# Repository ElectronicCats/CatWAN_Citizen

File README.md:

# CatWAN Citizen Sensor Board

LoRa Smart city sensor, based on open hardware and free software, generating and sharing real open data on air pollution, acoustics and many more, compatible with LoRa and LoRaWAN.

## Sensor list

|Metric|Units|Sensor|
|-|:-:|:-:|
| **Atmospheric Pressure** | Pa | BME280 |
| **Air Temperature / Relative Humidity** | ºC / %rh | BME280|
| **CO, eCO2** | ppm |AMS CCS811|
| **Noise Level and Spectrum** | dBa |Microphone|
| **Ambient Light** | lx | Rohm BEML6075 |

## LICENSE
Firmware released under an GNU AGPL v3.0 license. See the LICENSE file for more information.

Hardware released under an CERN Open Hardware Licence v1.2. See the LICENSE_HARDWARE file for more information.

Designed by Electronic Cats.

Electronic Cats is a registered trademark, please do not use if you sell these PCBs.

Electronic Cats invests time and resources providing this open source design, please support Electronic Cats and open-source hardware by purchasing products from Electronic Cats!

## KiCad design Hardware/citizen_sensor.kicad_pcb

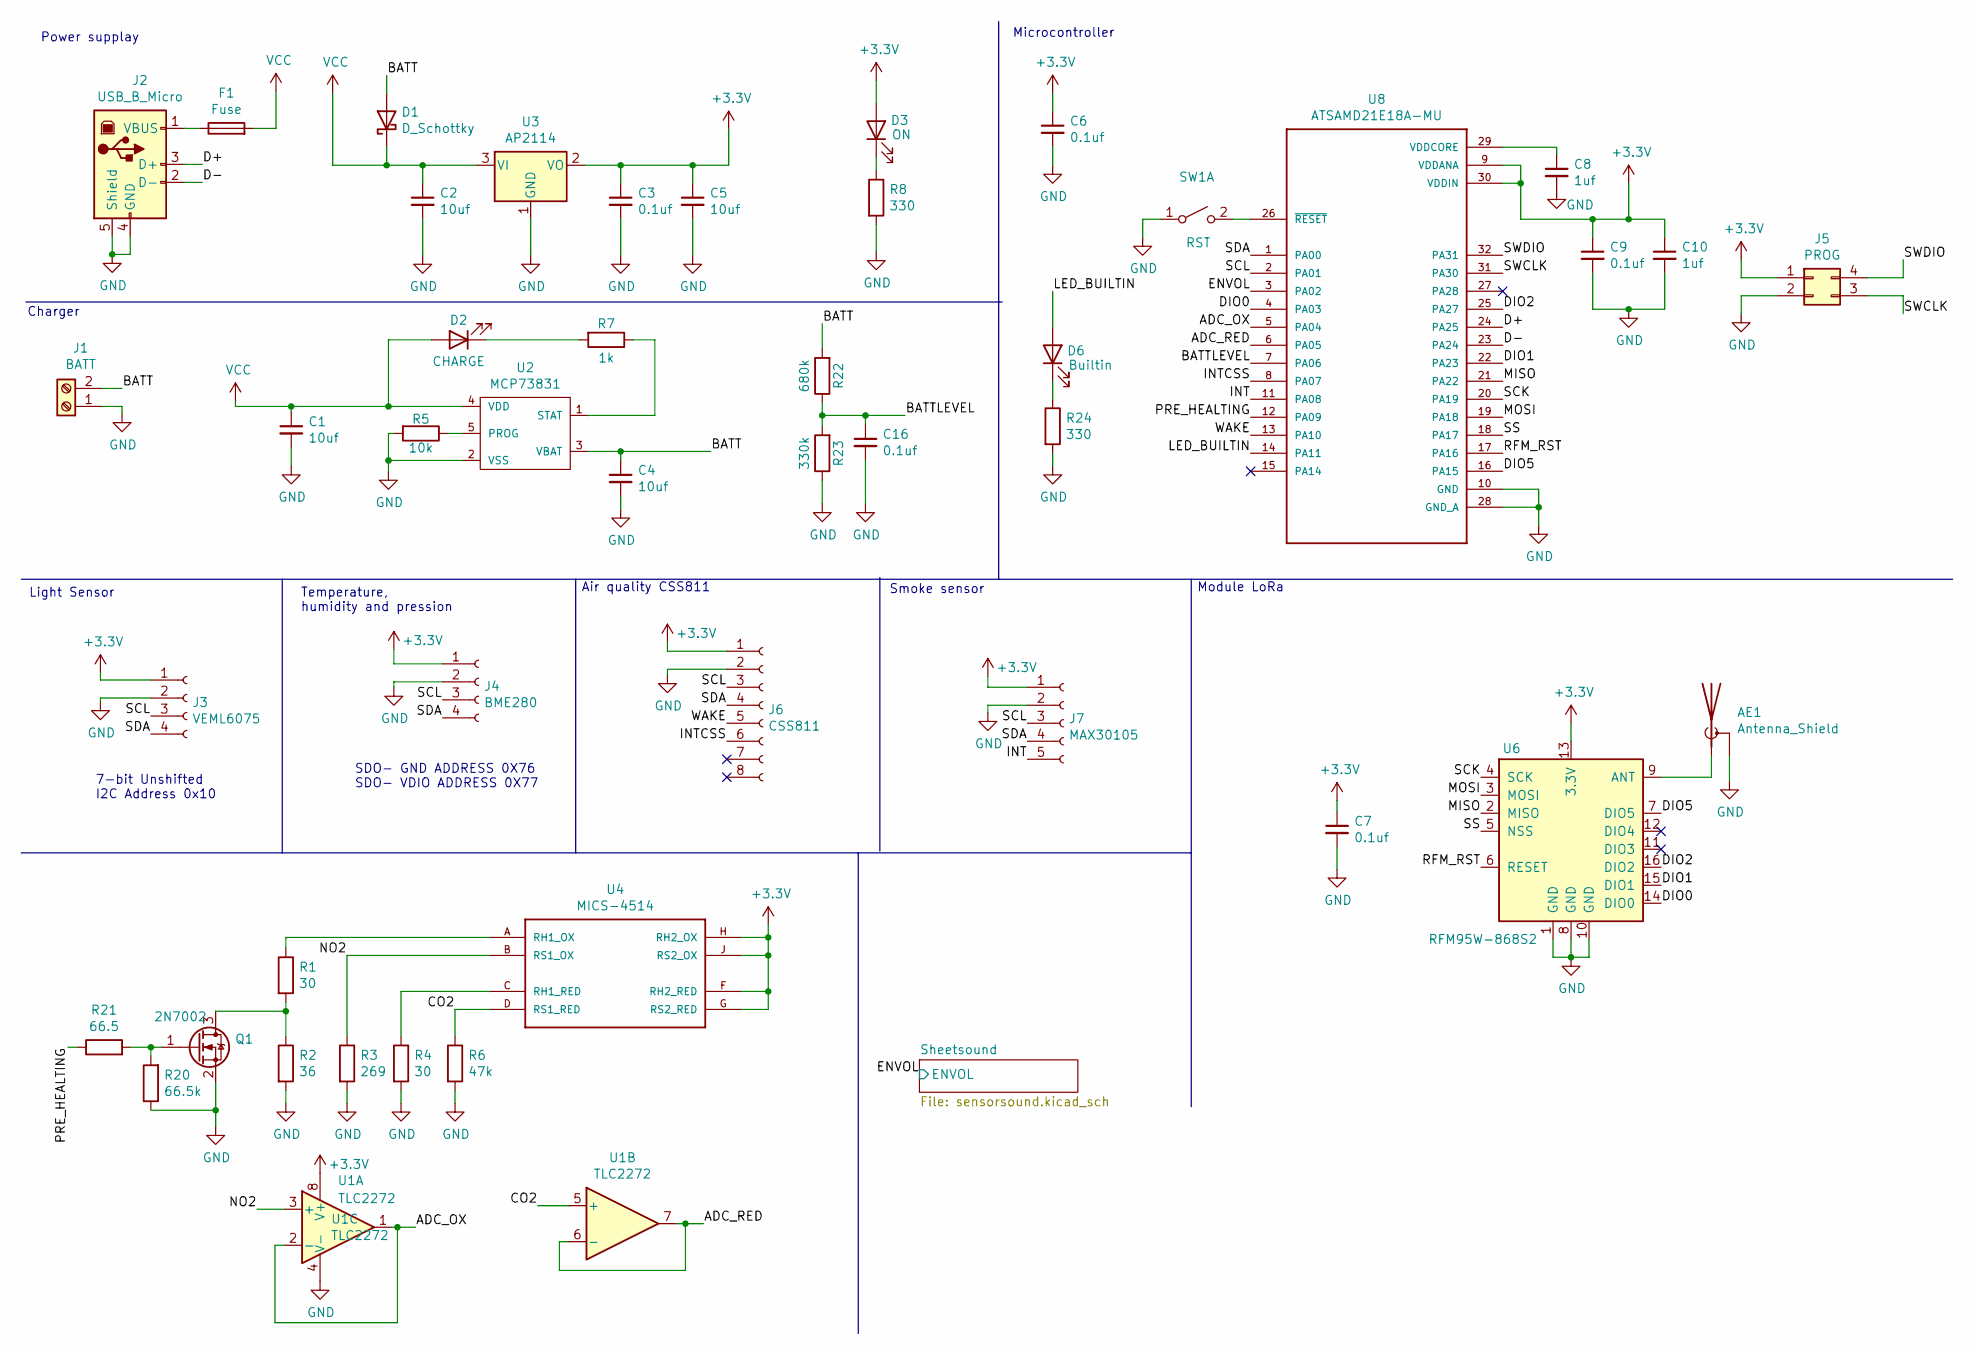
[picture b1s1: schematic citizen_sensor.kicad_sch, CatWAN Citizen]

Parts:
AE1: Antenna_Shield; AMPHENOL_901-144
C1, C2, C4, C5: 10uf; C_0805_2012Metric_Pad1.15x1.40mm_HandSolder
C3, C6, C7, C9, C16: 0.1uf; C_0805_2012Metric_Pad1.15x1.40mm_HandSolder
C8, C10: 1uf; C_0805_2012Metric_Pad1.15x1.40mm_HandSolder
D1: D_Schottky; D_SOD-123
D2: CHARGE; LED_0805_2012Metric_Castellated
D3: ON; LED_0805_2012Metric_Castellated
D6: Builtin; LED_0805_2012Metric_Castellated
F1: Fuse; Fuse_1812_4532Metric_Pad1.30x3.40mm_HandSolder
J1: BATT; TerminalBlock_4Ucon_1x02_P3.50mm_Vertical
J2: USB_B_Micro; USB_Micro-B_Wuerth_629105150521
J3: VEML6075; PinHeader_1x04_P2.54mm_Vertical
J4: BME280; PinHeader_1x04_P2.54mm_Vertical
J5: PROG; PinHeader_1x04_P2.54mm_Vertical
J6: CSS811; PinHeader_1x08_P2.54mm_Vertical
J7: MAX30105; PinHeader_1x05_P2.54mm_Vertical
Q1: 2N7002; SOT-23
R1, R4: 30; R_0805_2012Metric_Pad1.15x1.40mm_HandSolder
R2: 36; R_0805_2012Metric_Pad1.15x1.40mm_HandSolder
R3: 269; R_0805_2012Metric_Pad1.15x1.40mm_HandSolder
R5: 10k; R_0805_2012Metric_Pad1.15x1.40mm_HandSolder
R6: 47k; R_0805_2012Metric_Pad1.15x1.40mm_HandSolder
R7: 1k; R_0805_2012Metric_Pad1.15x1.40mm_HandSolder
R8, R24: 330; R_0805_2012Metric_Pad1.15x1.40mm_HandSolder
R20: 66.5k; R_0805_2012Metric_Pad1.15x1.40mm_HandSolder
R21: 66.5; R_0805_2012Metric_Pad1.15x1.40mm_HandSolder
R22: 680k; R_0805_2012Metric_Pad1.15x1.40mm_HandSolder
R23: 330k; R_0805_2012Metric_Pad1.15x1.40mm_HandSolder
SW1: RST; SW_SPST_TL3342
U1: TLC2272; SOIC-8_3.9x4.9mm_P1.27mm
U2: MCP73831; SOT-23-5
U3: AP2114; SOT-223-3_TabPin2
U4: MICS-4514; MICS_10-SMD
U6: RFM95W-868S2; RFM95W
U8: ATSAMD21E18A-MU; TQFP-32_7x7mm_P0.8mm

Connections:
+3V3: C3.1, C5.1, C6.1, C7.1, C9.1, C10.1, D3.2 (A), J3.1, J4.1, J5.1, J6.1, J7.1, U1.8 (V+), U3.2 (VO), U4.F (RH2_RED), U4.G (RS2_RED), U4.H (RH2_OX), U4.J (RS2_OX), U6.13 (3.3V), U8.9 (VDDANA), U8.30 (VDDIN); also elsewhere on the board
/ADC_OX: U1.1, U1.2 (-), U8.5 (PA04)
/ADC_RED: U1.6 (-), U1.7, U8.6 (PA05)
/BATT: C4.1, D1.2 (A), J1.2, R22.2, U2.3 (VBAT)
/BATTLEVEL: C16.1, R22.1, R23.2, U8.7 (PA06)
/CO2: R6.1, U1.5 (+), U4.D (RS1_RED)
/D+: J2.3 (D+), U8.24 (PA25)
/D-: J2.2 (D-), U8.23 (PA24)
/DIO0: U6.14 (DIO0), U8.4 (PA03)
/DIO1: U6.15 (DIO1), U8.22 (PA23)
/DIO2: U6.16 (DIO2), U8.25 (PA27)
/DIO5: U6.7 (DIO5), U8.16 (PA15)
/ENVOL: U8.3 (PA02); also elsewhere on the board
/INT: J7.5, U8.11 (PA08)
/INTCSS: J6.6, U8.8 (PA07)
/LED_BUILTIN: D6.2 (A), U8.14 (PA11)
/MISO: U6.2 (MISO), U8.21 (PA22)
/MOSI: U6.3 (MOSI), U8.19 (PA18)
/NO2: R3.1, U1.3 (+), U4.B (RS1_OX)
/PRE_HEALTING: R21.1, U8.12 (PA09)
/RFM_RST: U6.6 (RESET), U8.17 (PA16)
/SCK: U6.4 (SCK), U8.20 (PA19)
/SCL: J3.3, J4.3, J6.3, J7.3, U8.2 (PA01)
/SDA: J3.4, J4.4, J6.4, J7.4, U8.1 (PA00)
/SS: U6.5 (NSS), U8.18 (PA17)
/SWCLK: J5.3, U8.31 (PA30)
/SWDIO: J5.4, U8.32 (PA31)
/WAKE: J6.5, U8.13 (PA10)
GND: AE1.2 (Shield), C1.2, C2.2, C3.2, C4.2, C5.2, C6.2, C7.2, C8.2, C9.2, C10.2, C16.2, J1.1, J2.4 (GND), J2.5 (Shield), J3.2, J4.2, J5.2, J6.2, J7.2, Q1.2 (S), R2.2, R3.2, R4.2, R5.2, R6.2, R8.2, R20.1, R23.1, R24.2, SW1.1 (A), U1.4 (V-), U2.2 (VSS), U3.1 (GND), U6.1 (GND), U6.8 (GND), U6.10 (GND), U8.10 (GND), U8.28 (GND_A); also elsewhere on the board
unnamed: AE1.1 (A), U6.9 (ANT)
unnamed: C8.1, U8.29 (VDDCORE)
unnamed: D2.1 (K), R7.2
unnamed: D3.1 (K), R8.1
unnamed: D6.1 (K), R24.1
unnamed: F1.1, J2.1 (VBUS)
unnamed: Q1.1 (G), R20.2, R21.2
unnamed: Q1.3 (D), R1.2, R2.1
unnamed: R1.1, U4.A (RH1_OX)
unnamed: R4.1, U4.C (RH1_RED)
unnamed: R5.1, U2.5 (PROG)
unnamed: R7.1, U2.1 (STAT)
unnamed: SW1.2 (B), U8.26 (~RESET)
VCC: C1.1, C2.1, D1.1 (K), D2.2 (A), F1.2, U2.4 (VDD), U3.3 (VI)

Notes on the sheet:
Module LoRa
Microcontroller
Air quality CSS811
Smoke sensor
Power supplay
7-bit Unshifted I2C Address 0x10
Charger
Light Sensor
Temperature, humidity and pression
SDO- GND ADDRESS 0X76 SDO- VDIO ADDRESS 0X77

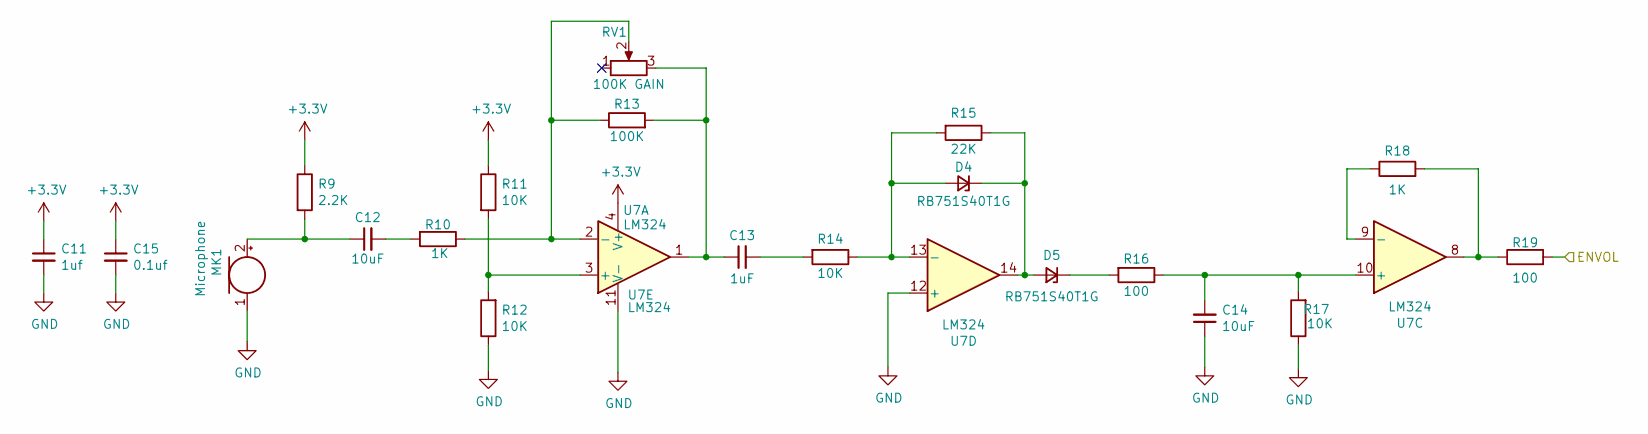
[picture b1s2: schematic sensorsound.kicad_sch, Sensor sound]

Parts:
C11: 1uf; C_0805_2012Metric_Pad1.15x1.40mm_HandSolder
C12, C14: 10uF; C_0805_2012Metric_Pad1.15x1.40mm_HandSolder
C13: 1uF; C_0805_2012Metric_Pad1.15x1.40mm_HandSolder
C15: 0.1uf; C_0805_2012Metric_Pad1.15x1.40mm_HandSolder
D4, D5: RB751S40T1G; D_SOD-123
MK1: Microphone; TerminalBlock_TE_282834-2_1x02_P2.54mm_Horizontal
R9: 2.2K; R_0805_2012Metric_Pad1.15x1.40mm_HandSolder
R10, R18: 1K; R_0805_2012Metric_Pad1.15x1.40mm_HandSolder
R11, R12, R14, R17: 10K; R_0805_2012Metric_Pad1.15x1.40mm_HandSolder
R13: 100K; R_0805_2012Metric_Pad1.15x1.40mm_HandSolder
R15: 22K; R_0805_2012Metric_Pad1.15x1.40mm_HandSolder
R16, R19: 100; R_0805_2012Metric_Pad1.15x1.40mm_HandSolder
RV1: 100K GAIN; Potentiometer_Bourns_3386P_Vertical
U7: LM324; SOIC-14_3.9x8.7mm_P1.27mm

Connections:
+3V3: C11.1, C15.1, R9.1, R11.1, U7.4 (V+); also elsewhere on the board
/ENVOL: R19.2; also elsewhere on the board
GND: C11.2, C14.1, C15.2, MK1.1 (-), R12.1, R17.1, U7.11 (V-), U7.12 (+); also elsewhere on the board
unnamed: C12.1, MK1.2 (+), R9.2
unnamed: C12.2, R10.2
unnamed: C13.1, R13.2, RV1.3, U7.1
unnamed: C13.2, R14.2
unnamed: C14.2, R16.1, R17.2, U7.10 (+)
unnamed: D4.1 (K), D5.2 (A), R15.1, U7.14
unnamed: D4.2 (A), R14.1, R15.2, U7.13 (-)
unnamed: D5.1 (K), R16.2
unnamed: R10.1, R13.1, RV1.2, U7.2 (-)
unnamed: R11.2, R12.2, U7.3 (+)
unnamed: R18.1, U7.9 (-)
unnamed: R18.2, R19.1, U7.8

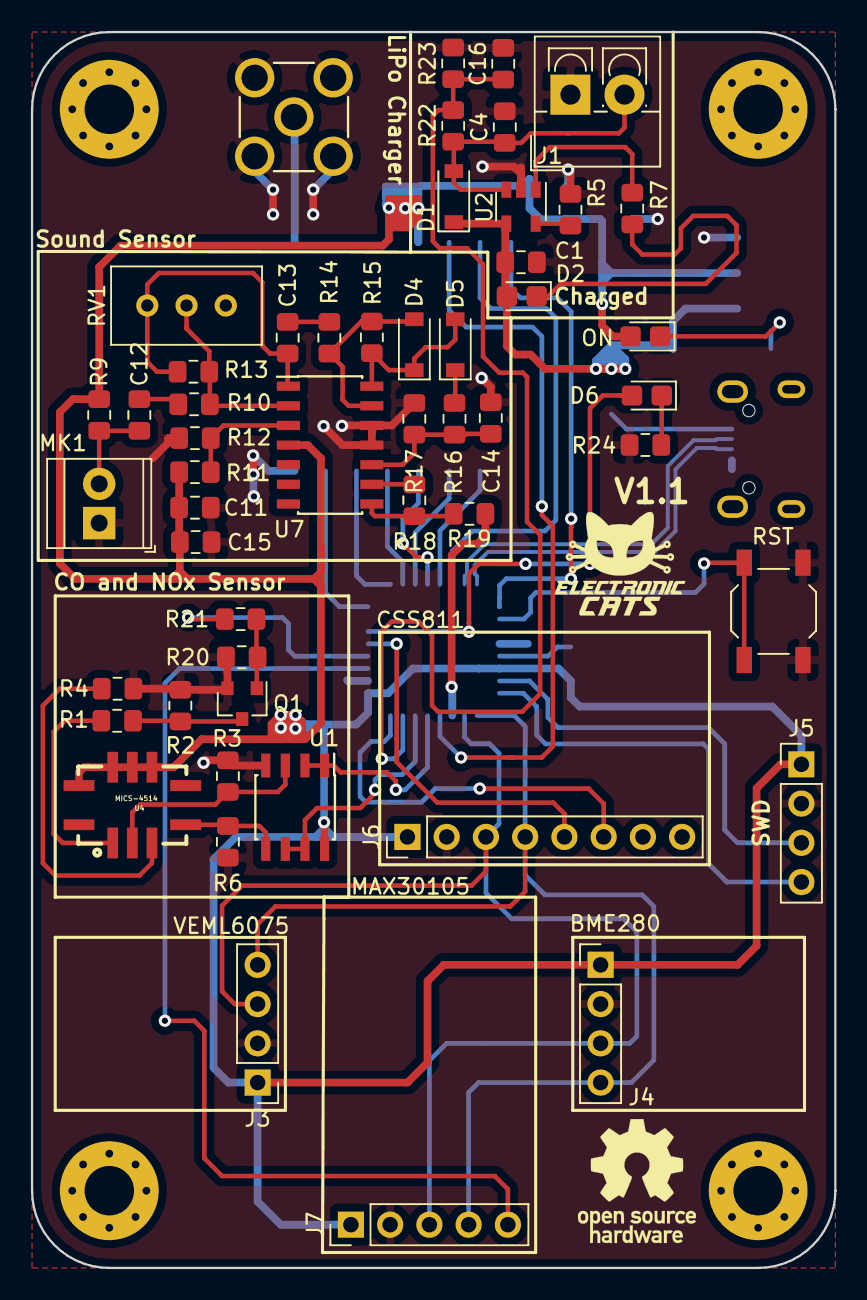
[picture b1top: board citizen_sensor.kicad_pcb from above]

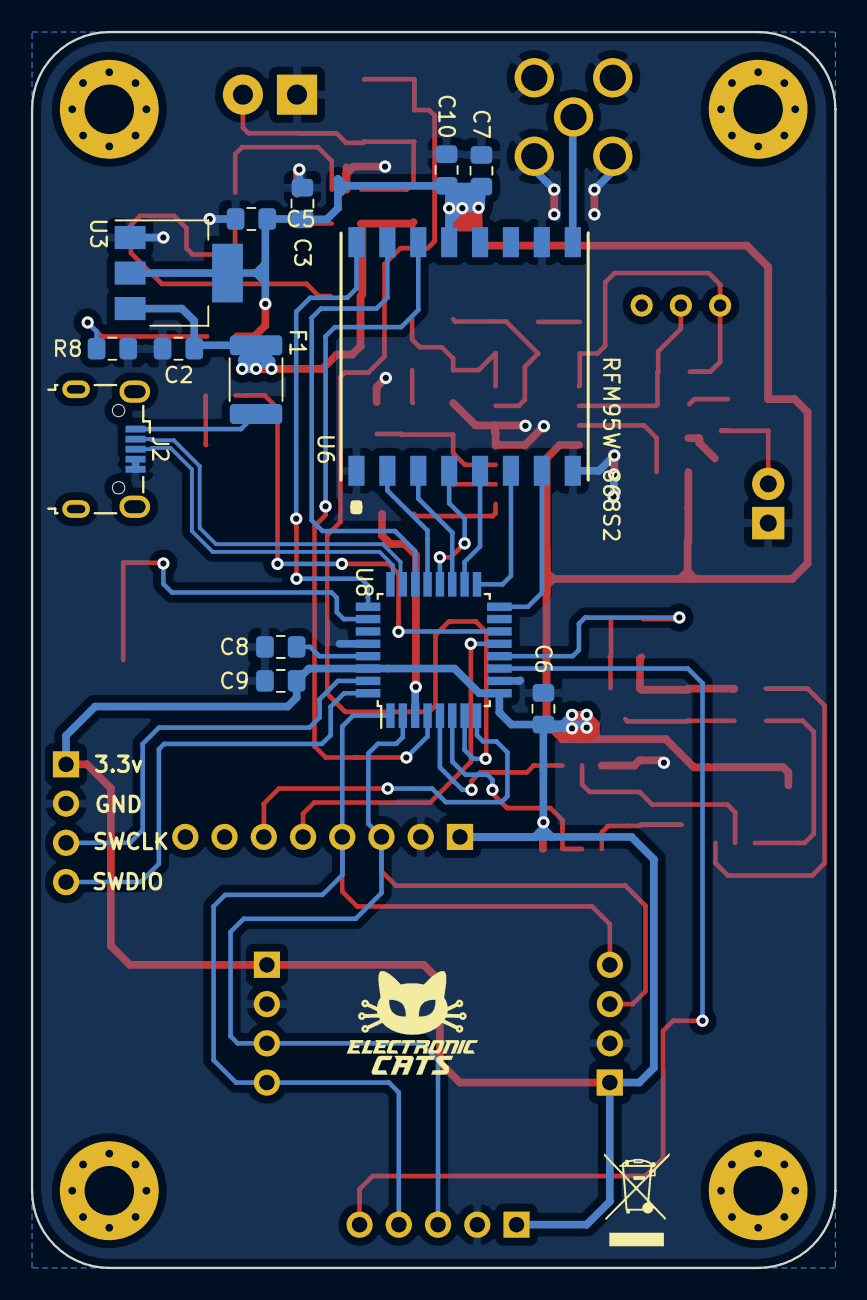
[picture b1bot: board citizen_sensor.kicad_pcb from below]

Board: 2 copper layers, 52.0 x 80.0 mm, 66 parts (14 on the bottom side), 55 nets.

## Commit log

2019-01-23 microcontroller and power supply
2019-01-23 readme
2019-01-23 charger
2019-01-23 modulation LoRa
2019-01-24 values capacitor and resistor
2019-01-24 light sensor
2019-01-24 move files
2019-01-24 Atmospheric sensor
2019-01-25 add sound sensor
2019-01-25 sound circuit ampli
2019-01-26 sensor sound envolvent
2019-01-26 change VCC with 3.3V sound sensor
2019-01-28 add capacitor VDDCORE
2019-01-29 add com I2C to samd
2019-01-29 add signal sound to samd
2019-01-29 charger fix
2019-01-31 change BME280 brakeout
2019-01-31 add circuit MICS4514
2019-01-31 move data name
2019-02-01 change veml6075 to brakeout
2019-02-05 ERC check
2019-02-05 footprints
2019-02-06 add fuse
2019-02-06 add manf# res cap
2019-02-06 BOM file .csv
2019-02-06 add cap amp voltage
2019-02-06 add BOM C15
2019-02-06 Bom form
2019-02-06 footprint c15
2019-02-08 footprint mics4514
2019-02-18 add css811
2019-02-18 voltaje divisor batt level
2019-02-18 PCB read net list
2019-02-19 Update description
2019-02-20 Update schematic
2019-02-20 Update netlist
2019-02-20 PCB routed 0.1v
2019-02-20 Add gitignore
2019-02-20 add logos
2019-02-20 add logo fablab yucatan ♥️
2019-02-21 Fix antenna and mounting holes
2019-02-21 fix VDD y GND of TLC2272
2019-02-22 Update mic
2019-02-23 Update pot
2019-02-23 Update metadata
2019-02-23 Update meta-data
2019-02-23 Update compnent placement and pot
2019-02-24 fabcity logo
2019-02-25 Change corners
2019-02-25 Change On LED
2019-02-25 Update components 3d
2019-02-25 Add 3D models
2019-02-25 Add photo renders
2019-02-28 Auto stash before merge of "master" and "origin/master"
    change resistor mics co
2019-03-20 Create LICENSE
2019-03-20 mover resistor to layer
2019-03-20 Revert "mover resistor to layer"
    This reverts commit 3cd94dc54691067b571b78a8cbe4544d7b6d2027.
2019-03-22 example read sensor css811
2019-03-23 change name files
2019-03-23 change name binder .ino
2019-03-23 add BMP280 read
2019-03-25 add OSHW MX0007
2019-03-26 add MICS4514 scketch
2019-03-28 send data BME280
2019-03-28 Add ccs and MICS sensors
2019-03-28 change name firmeware
2019-03-28 change equations example
2019-03-28 change equiation and send data
2019-04-01 changes commits by Eduardo
2019-04-01 change firmware name
2019-04-02 change equations sensor MICS
2019-04-05 example read VEML6075 "UV"
2019-04-05 add sensor uv to lpp library
2019-04-09 change resolution readanalog
2019-04-10 serial UV erayser delete
2019-04-10 serial print UV delete
2019-05-03 add read sound sensor
2019-05-07 read sound example
2019-05-07 change range
2019-05-09 add sound to sand data
2019-05-17 add label sheet
2019-06-10 chenge name BM208 to BME280
2019-06-10 add led builtin
2019-06-10 add led builtin en PCB
2019-06-10 Add V0.1 text
2020-02-22 Update Kicad5 and fix RESET CSS811
2020-02-22 Fix CCS811 read
2020-02-22 best comment CSS811 error
2020-02-22 remove inncesary variables
2020-02-22 port to library lorawan beelan
2020-02-22 add read battery
2020-02-22 Fix Index UV
2020-02-22 Add debug define
2020-02-25 change battery to analoginput
2020-02-27 Fix Battery analogInput
2020-03-04 Fixed channels ever
2022-05-14 add gitignore backups kicad
2022-05-14 update kicad 6
